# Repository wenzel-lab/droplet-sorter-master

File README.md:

# "Ritmos": Real-time Technology for Microfluidic Droplet Sorting  

Welcome to the main repository where we maintain the different documentation parts of the open source hardware flow-cytometer for Fluorescence Activated Droplet Sorting (FADS). The overaching aim of this project is to *open up* microfluidic experimentation, by creating a prototype instrument that is based on *connectable*, *open source hardware*, modern and *low-cost* components (such as RaspberryPi, RedPitaya. Adrunio, 3D printing, on-board components, open or at least accessible design software and operation software especially python). A key design element for this purpose is that the hardware and sorftware design is *easy to understand and modify for most interested scientists*, in contrast to many efforts in current Open Source FPGA development, which need substantive developer expertise. Currently, similar solutions in the lab come either in a "black-box instrument" as a commercial closed-source and non-modyfiable solution, or are assembled by scientists based on National Instruments FPGA cards with user-friendly yet obscure, expensive and closed-source LabView software libraries. Both solutions are not satisfying for the budget or modifyability of most academic labs in the world. Note that the design in this repository is quite different to literatures designs. The set-up has been designed to significantly lower cost (estimated parts cost 20-30k USD, mainly for optical filters, detectors and laser) and open source it, including hardware, software and accessible fabrication of parts where possible. Also, a number of updates and improvements have been made over the current state-of the art of droplet sorters, inspired by technical advances in the related field of flow-cytometry.

Follow us! [#twitter](https://twitter.com/WenzelLab), [#YouTube](https://www.youtube.com/@librehub), [#LinkedIn](https://www.linkedin.com/company/92802424), [#instagram](https://www.instagram.com/wenzellab/), [#Printables](https://www.printables.com/@WenzelLab), [#LIBREhub website](https://librehub.github.io), [#IIBM website](https://ingenieriabiologicaymedica.uc.cl/en/people/faculty/821-tobias-wenzel)

## Components of this project

* FPGA-powered and Python-based open source workstation controller [Ritmos Conductor](https://github.com/wenzel-lab/droplet-sorting-FPGA-controller/tree/master), built on a stripped-down version of [PyRPL](https://github.com/wenzel-lab/pyrpl), designed to run on a Red Pitaya single board computer.

* [Graphical User Interface (GUI)](https://github.com/wenzel-lab/droplet-sorter-GUI) of the droplet sorter, designed with Bokeh (Python) to run on an independent computer. It uncludes a WebSocket webserver that communicates with the RedPitaya board.

* [Robotic positioning stage](https://github.com/wenzel-lab/squid-motorized-stage) for microfluidic sorting chips, with it's own [stage controller software](https://github.com/wenzel-lab/droplet-sorter-stage-software), of course written in python. The optoelectronic assembly is highly based on digital fabriaction, especially 3d printing, to increase accessibility and modifiability.

* [Custom multiplexer board](https://github.com/wenzel-lab/droplet-sorter-master/tree/main/multiplexer-board) to expand the two fast analogue detector inputs of the RedPitaya computer to six channels by multiplexing, as well as communication with the pulse generation board and detector bias voltages.

* [High voltage sorting pulse generation board](https://github.com/wenzel-lab/high-voltage-pulse-generator/)

* [Open source microfluidic flow controller](https://github.com/wenzel-lab/modular-microfluidics-workstation-controller)

## Background - sorting of microfluidic droplets

If you are wondering what the sorting of microfluidic droplets is, we reccomend the following litertature:
* The original [droplet sorting publication (2009)](https://doi.org/10.1039/b902504a) using electrical droplet actuacion and fluorescence detection.
* A review of [active droplet sorting methods (2017)](https://doi.org/10.1039/c6lc01435f ), inclduing alternatives to the dielectrophoresis used here.
* A review of [advances on sorting and detection methods (2021)](https://doi.org/10.3389/fchem.2021.666867) in the context of directed enzyme evolution.
* And a [detailed protocol (2023)](https://doi.org/10.1038/s41596-022-00796-2) of how to assemble a current state-of-the-art droplet sorting set-up with propriatory parts and LabView, similar to the set-ups that exsist in several research labs around the world (estimated parts costs 200.000 USD).
* Since recently, there are also commercial solutions available (for a significantly higher cost and non-modyfiable, but convenient to buy and use), especially the [Styx](https://atrandi.com/styx), [Pico-Mine](https://spherefluidics.com/our-products/platform-products/cyto-mine/), [On-Chip Sort](https://on-chipbio.com/#link02).

## Preview of the components 

Our current sorter implementation uses a [custom multiplexer board](https://github.com/wenzel-lab/droplet-sorter-master/tree/main/multiplexer-board) to expand the two fast analogue imputs (for the use of two detectors) of the RedPitaya computer and FPG board to the use of six channels by multiplexing one of the analoguse imputs. The board also replicates the pins of the RedPitaya board for additional interfaces, for example with our pulse generator (see below) and the bias voltage control of the detectors. A future version implementation of the sorting controll is the making, where we use the RedPitaya X-channel system to add pairs of analogue inputs (and therefore detector inputs) to the capability of the stack, which is faster and more expandable.

Our robotic positioning stage. In the image on the right, you can see in blue all the pieces in the assembly that are 3d printed.

And our otptical detection arm assembly is based on the [Open-UC2 3d printed optics cubes](https://github.com/openUC2/UC2-GIT). The modified and new Open-UC2 compatible cubes can be found in the STL folder of this repository, and all modifyable design files are openly availble in the cloud [here on OnShape](https://tinyurl.com/WenzelLabUC2), where you can view, export and copy (to modify) the project designs.

Droplets are moved using our [microfluidics controller](https://github.com/wenzel-lab/modular-microfluidics-workstation-controller)

## Commercial and OEM components

For our implementation, we use a [compact OEM low-noise 3-laser module with eliptical beam forming](https://github.com/wenzel-lab/droplet-sorter-master/blob/main/docs/Laser_spec_PEC-410%20800049%20LRBV-FS-118%20Specification%20V01%20211012.pdf), to illuminate the sorting channel from above, so that we can also detect a lable-free side scattering signal in the detection arm.

We use the [MER2-160-227U3M-L camera](https://github.com/wenzel-lab/droplet-sorter-master/blob/main/docs/MER2-160-227U3MC(-L)-Datasheet%20mono%20high%20speed.pdf), a compact monochrome USB3 camera with the Sony IMX273 CMOS sensor, for fast framerate and triggering for strobe-illumination.

We also use modern [SiPM detectors from KETEK](https://github.com/wenzel-lab/droplet-sorter-master/blob/main/docs/KETEK-PE3315-WL-TIA-SP.pdf) that are both lower in cost and higher in performance compared to traditionally used PMT modules (lower dark noise, broader sensitive range, and they don't break when illuminated accidentally), but unfortunately the producer KETEK was recently purchased by Broadcom and they have discontinued this line of products, which means that currently more expensive competitor producs (be it PMTs, SiPMs or APDs) have to be used for new implementations of the sorter. In the end, the detector module types makes no difference for the assembly of the sorter, because it is agnostic to what module passes the voltage signal to the FPGA-board inputs.

## Optical filters used:

Please [handle optical filters with care](https://github.com/wenzel-lab/droplet-sorter-master/blob/main/docs/Handling%20of%20optical%20filters.pdf)!

| Filter | Type | supplier |
| :---   | :---  | :--- |
| FF01-561/14-25   | Bandpass filter to clean Lime-LED spectrum  | [AHF](https://ahf.de/produkte/spektralanalytik-photonik/optische-filter/einzelfilter/bandpass-filter/500-599-nm/561-14-brightline-hc/F39-563)    |
| ZET405/488/640m     | Tri-band filter to only block laser lines from camera | [Chroma](https://www.chroma.com/products/parts/zet405-488-640m)    |
| Di03-R405/488/561/635-t1-25x36   | 4-band beamsplitter to seperate scattering from fluorescence | [Laser2000](Di03-R405/488/561/635-t1-25x36)    |
| FF02-482/18-25   | Bandpass for 488nm laser scattering detection   | [AHF](https://ahf.de/produkte/spektralanalytik-photonik/optische-filter/einzelfilter/bandpass-filter/400-499-nm/482-18-brightline-hc/F39-483)    |
| glass slide     | to couple 4% reflected blue LED light into the beampath for alignment     | none    |
| FF01-446/523/600/677-25 | 4-band blocking filter for all fluorescence channels | [AHF](https://ahf.de/produkte/spektralanalytik-photonik/optische-filter/einzelfilter/bandpass-filter/multiband-filter/446-523-600-677-hc-quadband-filter/F72-866)    |
| FF555-Di03-25x36    | Central dichroic beam splitter between fluorescence channels | [AHF](https://ahf.de/produkte/spektralanalytik-photonik/optische-filter/strahlenteiler/epi-fluoreszenz-strahlenteiler/standard-strahlenteiler/langpass/strahlenteiler-hc-555/F38-555)    |
| FF495-Di03-25x36   | dichroic beam splitter to seperate blue and green fluorescence   | [AHF](https://ahf.de/produkte/spektralanalytik-photonik/optische-filter/strahlenteiler/epi-fluoreszenz-strahlenteiler/standard-strahlenteiler/langpass/strahlenteiler-hc-495/F38-495)    |
| T640LPXR   | dichroic beam splitter to seperate red and orange fluorescence      | [AHF](https://ahf.de/produkte/spektralanalytik-photonik/optische-filter/strahlenteiler/epi-fluoreszenz-strahlenteiler/standard-strahlenteiler/langpass/strahlenteiler-t-640-lpxr/F48-642)    |
| FF01-445/20-25   | bandpass filter blue    | [AHF](https://ahf.de/produkte/spektralanalytik-photonik/optische-filter/einzelfilter/bandpass-filter/400-499-nm/445-20-brightline-hc/F39-445)    |
| FF01-525/30-25   | bandpass filter green    | [AHF](https://ahf.de/produkte/spektralanalytik-photonik/optische-filter/einzelfilter/bandpass-filter/500-599-nm/525-30-brightline-hc/F37-526)    |
| FF01-600/37-25   | bandpass filter orange    | [AHF](https://ahf.de/produkte/spektralanalytik-photonik/optische-filter/einzelfilter/bandpass-filter/600-699-nm/600-37-brightline-hc/F39-637)    |
| FF01-697/58-25   | bandpass filter red     | [AHF](https://ahf.de/produkte/spektralanalytik-photonik/optische-filter/einzelfilter/bandpass-filter/600-699-nm/697-58-brightline-hc/F37-697)    |

## Contribute

This is an open project in the Wenzel Lab in Santiago, Chile. If you have any suggestions to improve it or add any additional functions make a pull-request or [open an issue](https://github.com/wenzel-lab/droplet-sorter-master/issues/new).
For interactions in our team and with the community applies the [GOSH Code of Conduct](https://openhardware.science/gosh-2017/gosh-code-of-conduct/).

## License

[CERN OHL 2W](LICENSE) © Nicolas Peschke, Matias Hurtado and Tobias Wenzel. This project is Open Source Hardware - please acknowledge us when using the hardware or sharing modifications.

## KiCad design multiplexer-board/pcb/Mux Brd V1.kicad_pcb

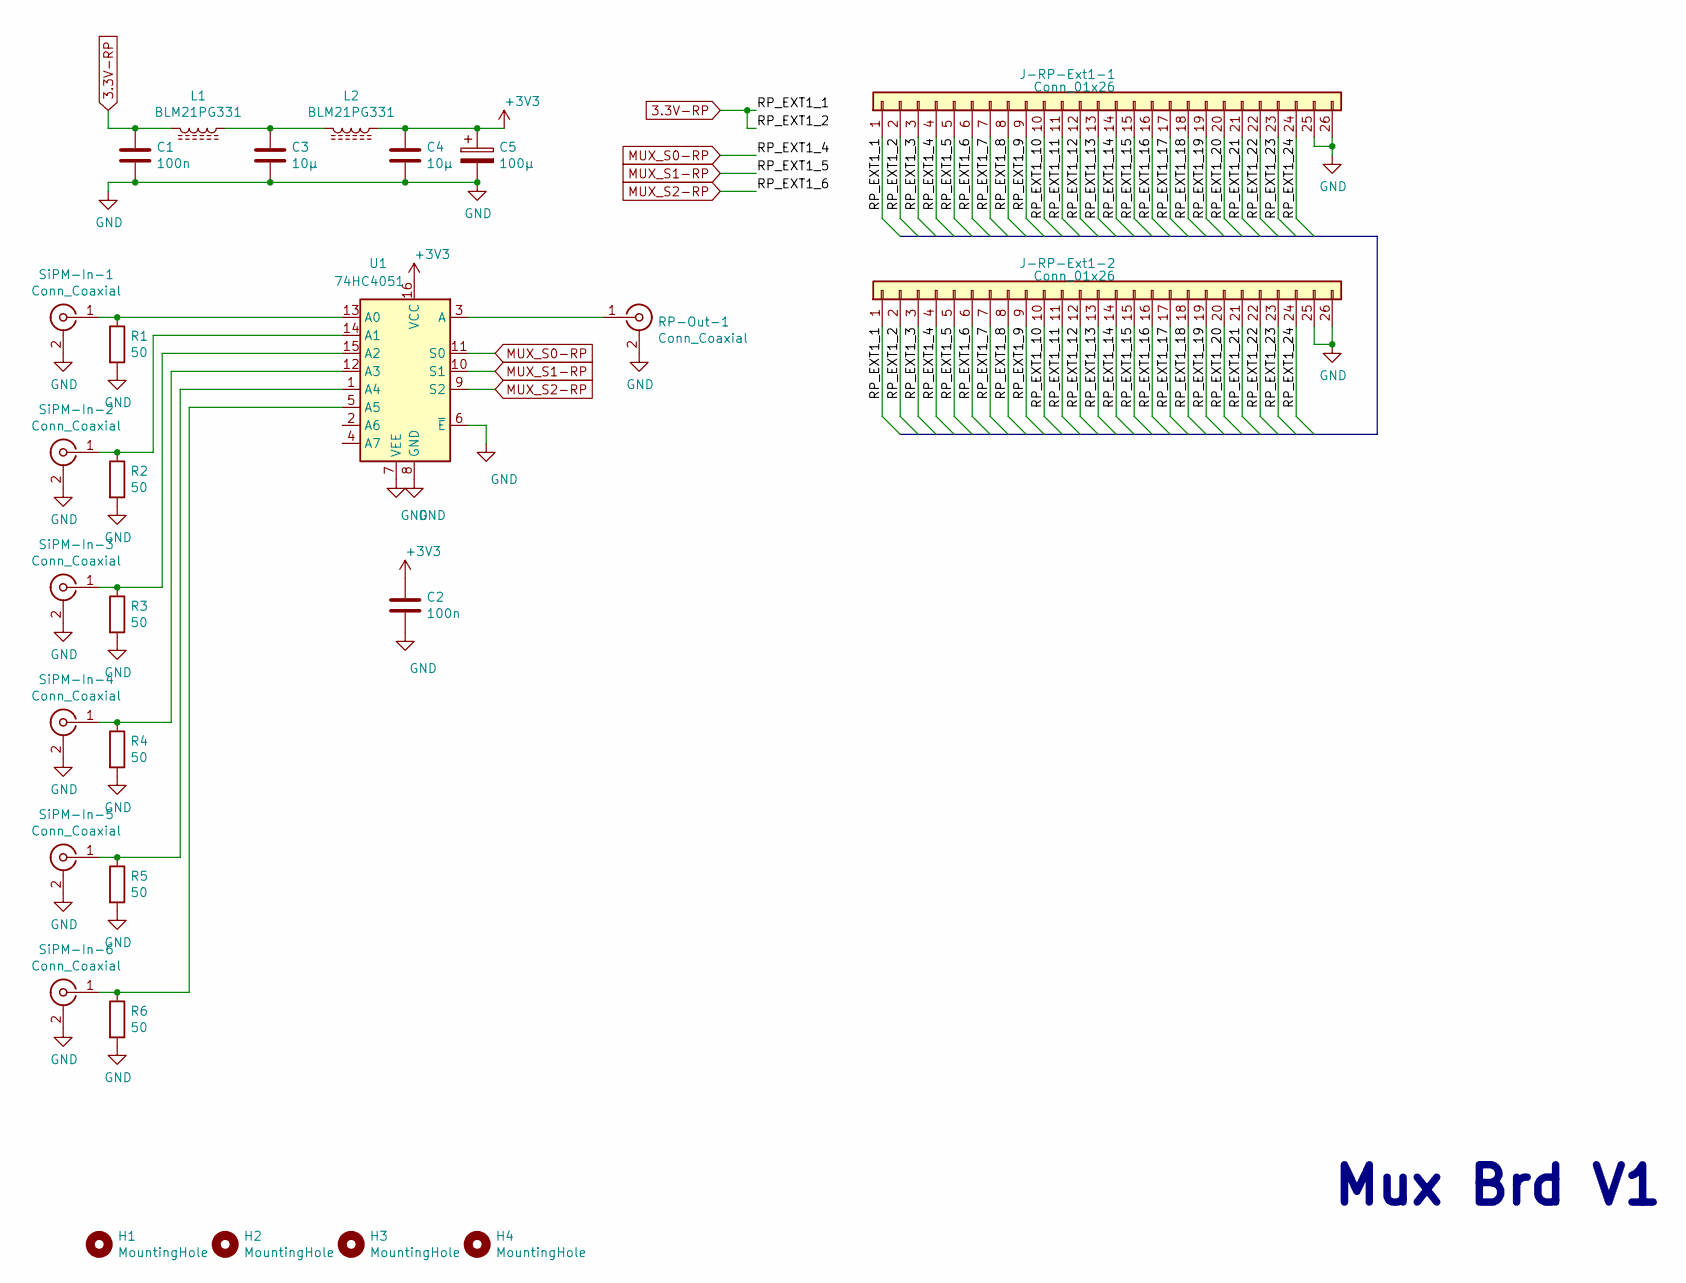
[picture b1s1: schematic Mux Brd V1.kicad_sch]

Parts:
C1, C2: 100n; C_0805_2012Metric_Pad1.18x1.45mm_HandSolder
C3, C4: 10µ; C_1206_3216Metric_Pad1.33x1.80mm_HandSolder
C5: 100µ; CP_Elec_6.3x7.7
H1, H2, H3, H4: MountingHole; MountingHole_3.2mm_M3_ISO7380
J-RP-Ext1-1, J-RP-Ext1-2: Conn_01x26; IDC-Header_2x13_P2.54mm_Vertical
L1, L2: BLM21PG331; L_0805_2012Metric_Pad1.15x1.40mm_HandSolder
R1, R2, R3, R4, R5, R6: 50; R_0805_2012Metric_Pad1.20x1.40mm_HandSolder
RP-Out-1: Conn_Coaxial; RFSOLUTIONS_CON-SMA-EDGE-S
SiPM-In-1, SiPM-In-2, SiPM-In-3, SiPM-In-4, SiPM-In-5, SiPM-In-6: Conn_Coaxial; RFSOLUTIONS_CON-SMA-EDGE-S
U1: 74HC4051; DIP-16_W7.62mm_Socket_LongPads

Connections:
3.3V-RP: C1.1, J-RP-Ext1-1.1, J-RP-Ext1-1.2, J-RP-Ext1-2.1, J-RP-Ext1-2.2, L1.2
+3V3: C2.1, C4.1, C5.1, L2.1, U1.16 (VCC)
/RP_EXT1_3: J-RP-Ext1-1.3, J-RP-Ext1-2.3
/RP_EXT1_7: J-RP-Ext1-1.7, J-RP-Ext1-2.7
/RP_EXT1_8: J-RP-Ext1-1.8, J-RP-Ext1-2.8
/RP_EXT1_9: J-RP-Ext1-1.9, J-RP-Ext1-2.9
/RP_EXT1_10: J-RP-Ext1-1.10, J-RP-Ext1-2.10
/RP_EXT1_11: J-RP-Ext1-1.11, J-RP-Ext1-2.11
/RP_EXT1_12: J-RP-Ext1-1.12, J-RP-Ext1-2.12
/RP_EXT1_13: J-RP-Ext1-1.13, J-RP-Ext1-2.13
/RP_EXT1_14: J-RP-Ext1-1.14, J-RP-Ext1-2.14
/RP_EXT1_15: J-RP-Ext1-1.15, J-RP-Ext1-2.15
/RP_EXT1_16: J-RP-Ext1-1.16, J-RP-Ext1-2.16
/RP_EXT1_17: J-RP-Ext1-1.17, J-RP-Ext1-2.17
/RP_EXT1_18: J-RP-Ext1-1.18, J-RP-Ext1-2.18
/RP_EXT1_19: J-RP-Ext1-1.19, J-RP-Ext1-2.19
/RP_EXT1_20: J-RP-Ext1-1.20, J-RP-Ext1-2.20
/RP_EXT1_21: J-RP-Ext1-1.21, J-RP-Ext1-2.21
/RP_EXT1_22: J-RP-Ext1-1.22, J-RP-Ext1-2.22
/RP_EXT1_23: J-RP-Ext1-1.23, J-RP-Ext1-2.23
/RP_EXT1_24: J-RP-Ext1-1.24, J-RP-Ext1-2.24
GND: C1.2, C2.2, C3.2, C4.2, C5.2, J-RP-Ext1-1.25, J-RP-Ext1-1.26, J-RP-Ext1-2.25, J-RP-Ext1-2.26, R1.2, R2.2, R3.2, R4.2, R5.2, R6.2, RP-Out-1.2 (Ext), SiPM-In-1.2 (Ext), SiPM-In-2.2 (Ext), SiPM-In-3.2 (Ext), SiPM-In-4.2 (Ext), SiPM-In-5.2 (Ext), SiPM-In-6.2 (Ext), U1.6 (~E), U1.7 (VEE), U1.8 (GND)
MUX_S0-RP: J-RP-Ext1-1.4, J-RP-Ext1-2.4, U1.11 (S0)
MUX_S1-RP: J-RP-Ext1-1.5, J-RP-Ext1-2.5, U1.10 (S1)
MUX_S2-RP: J-RP-Ext1-1.6, J-RP-Ext1-2.6, U1.9 (S2)
unnamed: C3.1, L1.1, L2.2
unnamed: R1.1, SiPM-In-1.1 (In), U1.13 (A0)
unnamed: R2.1, SiPM-In-2.1 (In), U1.14 (A1)
unnamed: R3.1, SiPM-In-3.1 (In), U1.15 (A2)
unnamed: R4.1, SiPM-In-4.1 (In), U1.12 (A3)
unnamed: R5.1, SiPM-In-5.1 (In), U1.1 (A4)
unnamed: R6.1, SiPM-In-6.1 (In), U1.5 (A5)
unnamed: RP-Out-1.1 (In), U1.3 (A)

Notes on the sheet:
Mux Brd V1

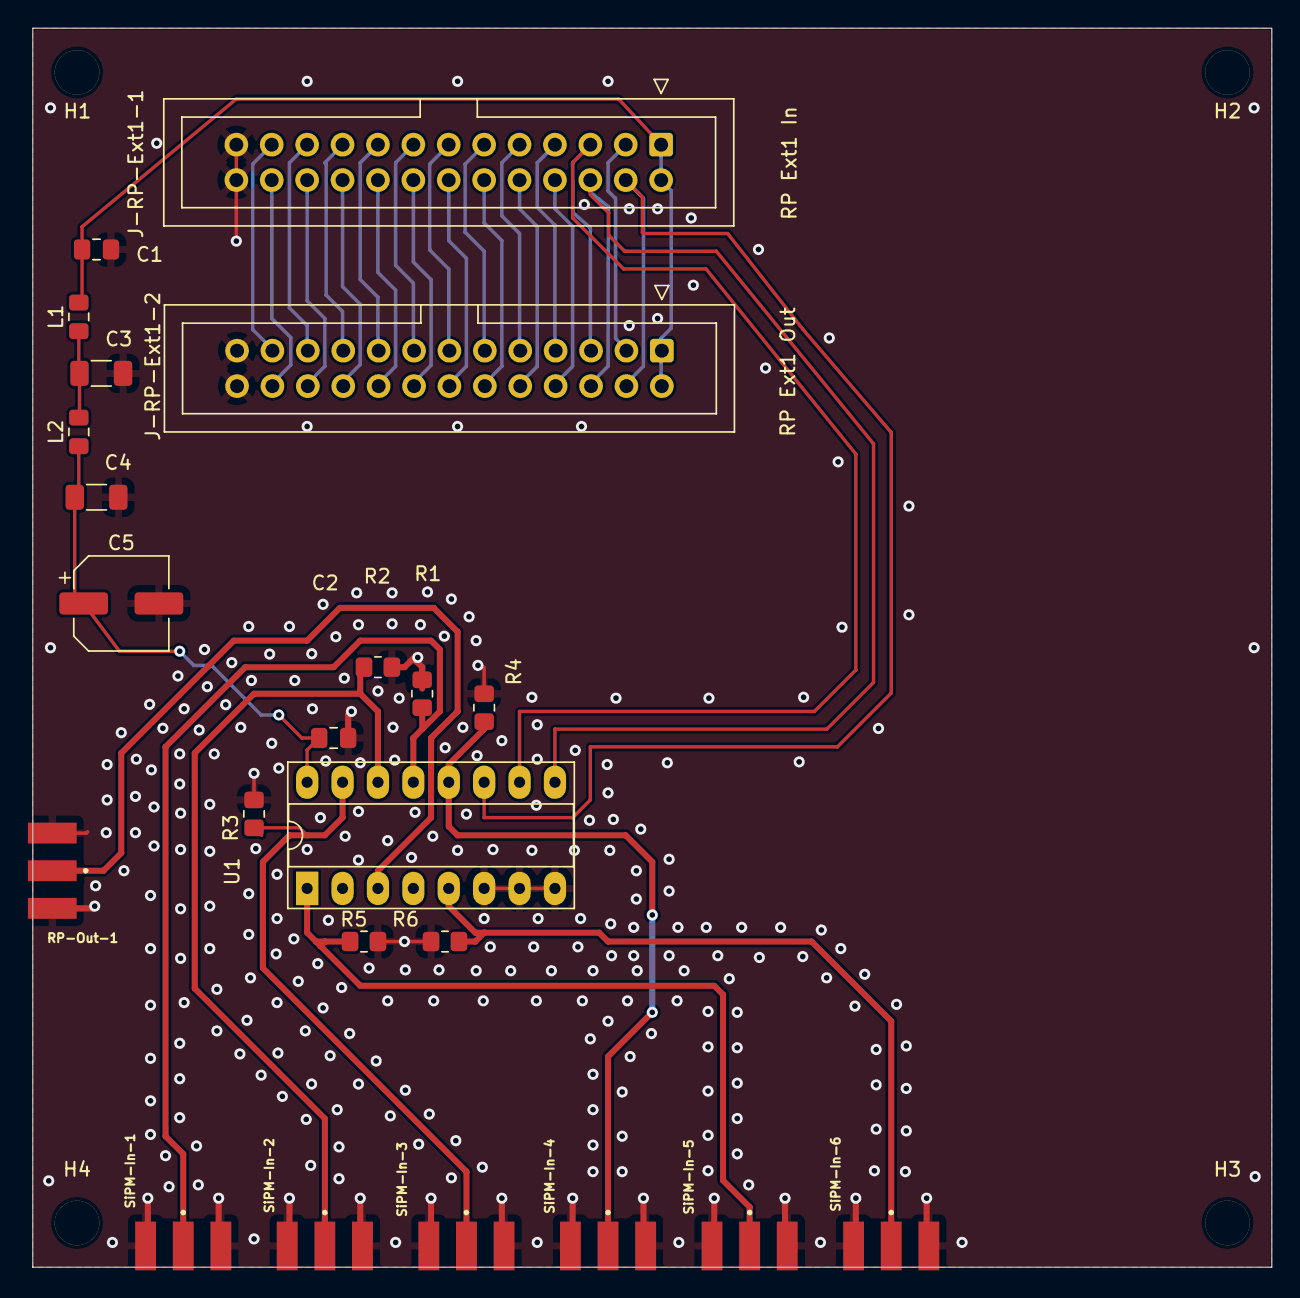
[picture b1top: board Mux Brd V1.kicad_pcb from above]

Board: 2 copper layers, 88.9 x 88.9 mm, 27 parts (0 on the bottom side), 33 nets.

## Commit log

2024-04-07 Rename laser_setup_droplet_sorting 5.png to laser_setup_droplet_sorting5.png
2024-04-07 add license file
2024-04-07 Update README.md
    update image placement
2024-04-11 Update README.md
    adding link to GUI repository
2024-04-11 Update README.md
    update cytometer CAD overview
2024-04-18 Update README.md
    add stage software repo link
2024-04-18 Update README.md
    update link
2024-05-14 Update README.md
    Give the instrument a name!
2024-05-14 Update README.md
    layout tweaks
2024-05-14 Update README.md
    updates renderings
2024-05-14 Update README.md
    layout updates, added image
2024-05-14 Update README.md
    fix spelling
2024-05-14 Update README.md
    specify cost context.
2024-05-20 Update README.md
    Add optical filter information
2024-06-20 add files for multiplexer pcb
2024-06-20 Create test
2024-07-09 Update README.md
    Add the link to the amplifier repository
2024-07-09 add files from optomechanics repository
2025-01-13 Update README.md
    restructure components of the project part to allow faster overview and easier access to sub-repositories.
2025-12-08 add pcb design
